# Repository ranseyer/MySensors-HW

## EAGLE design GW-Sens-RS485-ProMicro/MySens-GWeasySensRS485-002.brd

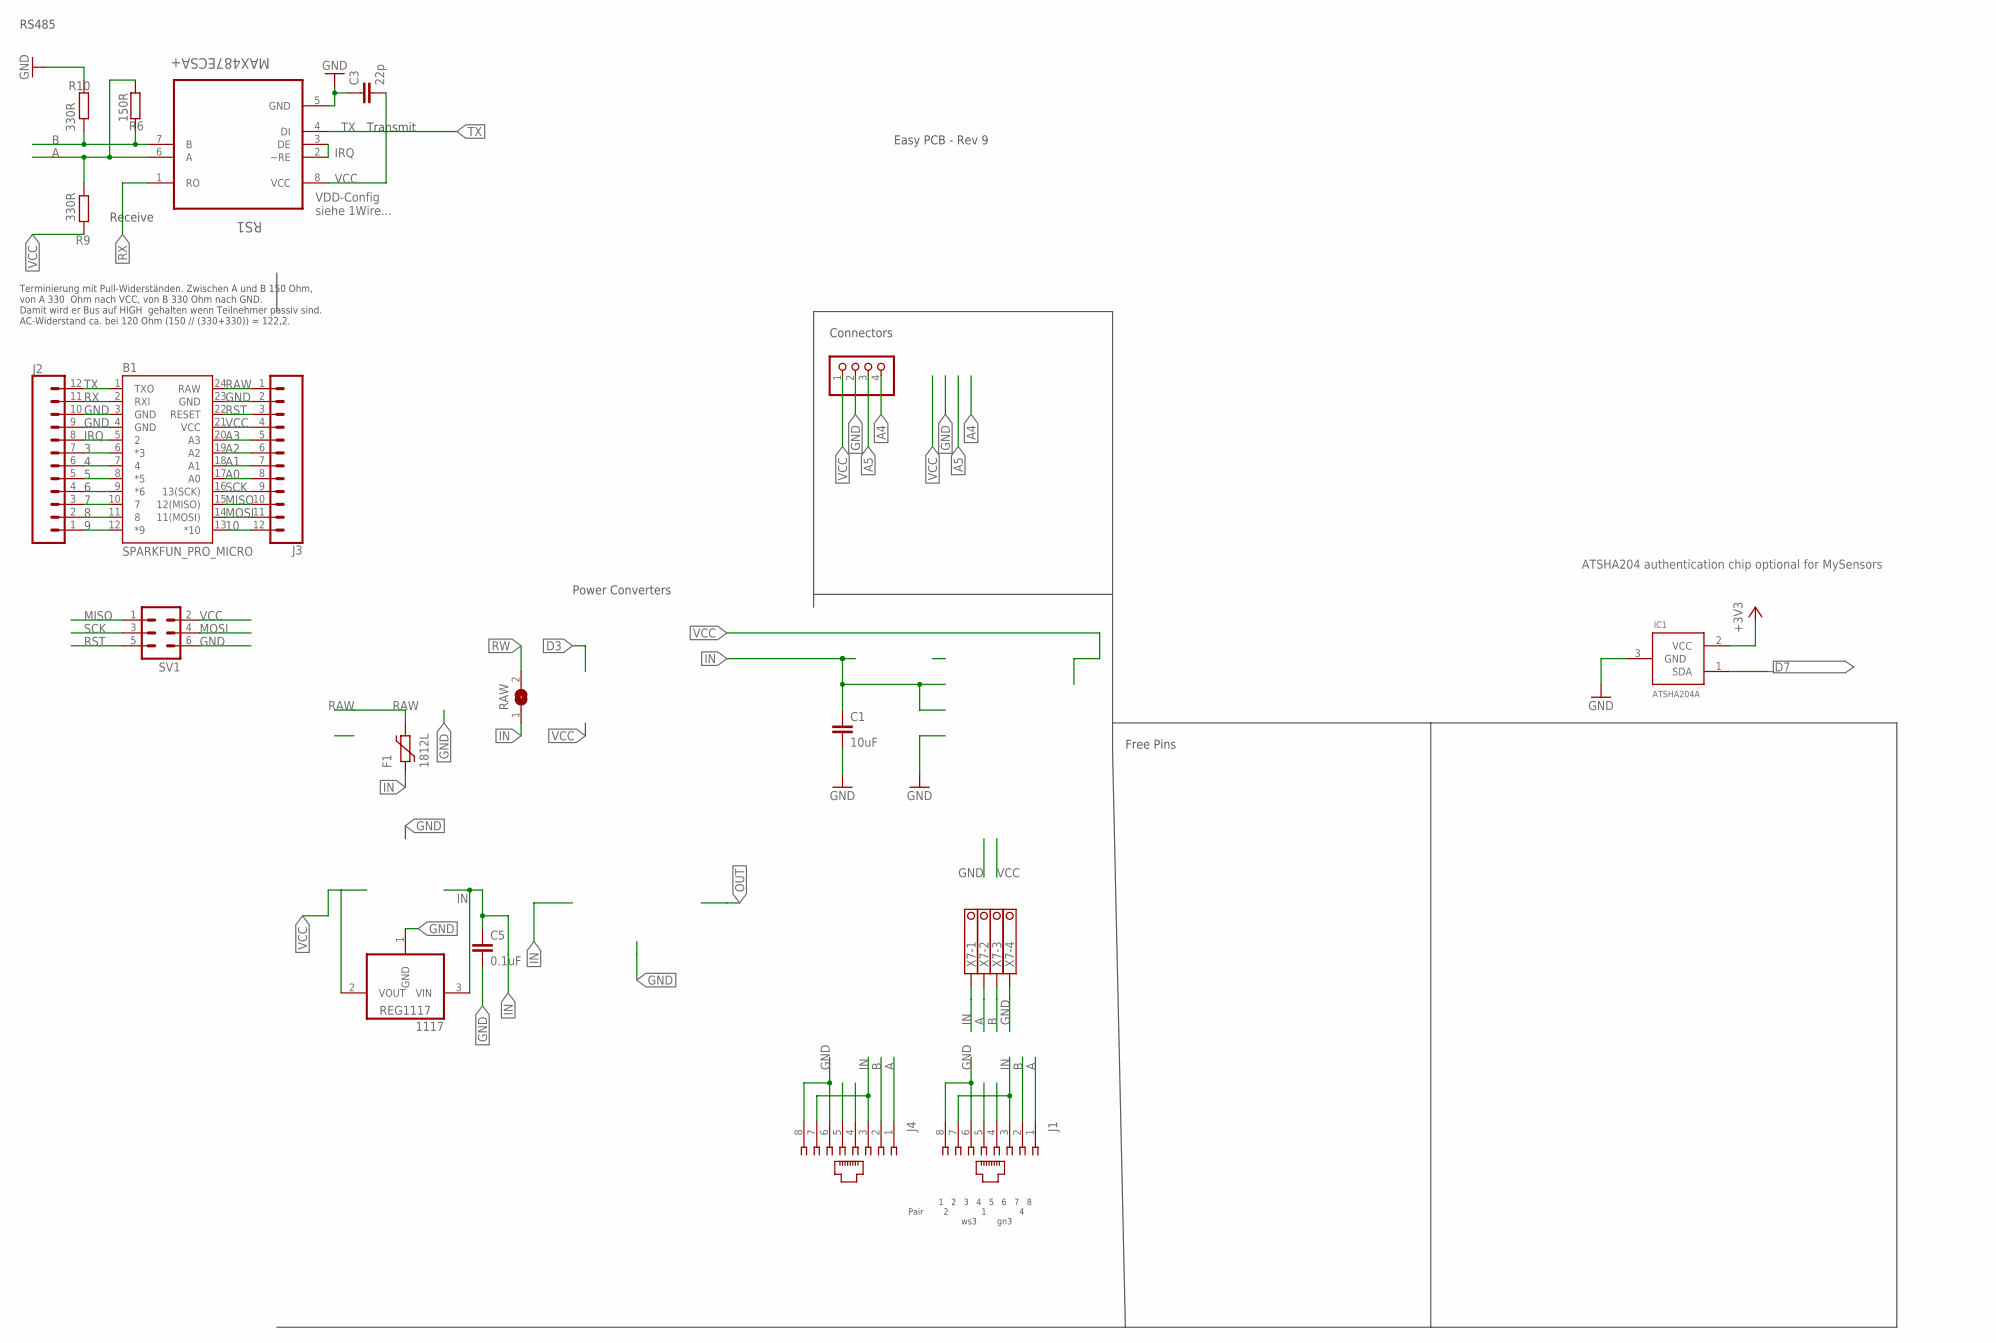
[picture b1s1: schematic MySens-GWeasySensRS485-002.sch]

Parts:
1117: REG1117; SOT223
B1: SPARKFUN_PRO_MICRO
C1: 10uF; 0805
C3: 22p; C0805
C5: 0.1uF; C1206
F1: 1812L
IC1: ATSHA204A; SOT23
J1, J4: 215878-2
J2, J3: CONN_12; 1X12
JP10: PINHD-1X04_2.54-S; 1X04-S
R6: 150R; R0805
R9, R10: 330R; R0805
RAW: SJ
RS1: MAX487ECSA+; SOIC127P600X175-8N
SV1: MA03-2
X7: 1751264

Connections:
3: B1.6 (*3), J2.7
3V3: IC1.2 (VCC)
4: B1.7 (4), J2.6
5: B1.8 (*5), J2.5
6: B1.9 (*6), J2.4
7: B1.10 (7), J2.3
8: B1.11 (8), J2.2
9: B1.12 (*9), J2.1
10: B1.13 (*10), J3.12
A: J1.1, J4.1, R6.1, R9.2, RS1.6 (A), X7.2
A0: B1.17 (A0), J3.8
A1: B1.18 (A1), J3.7
A2: B1.19 (A2), J3.6
A3: B1.20 (A3), J3.5
A4: JP10.4
A5: JP10.3
B: J1.2, J4.2, R6.2, R10.1, RS1.7 (B), X7.3
D7: IC1.1 (SDA)
GND: 1117.1 (GND), B1.3 (GND), B1.4 (GND), B1.23 (GND), C1.2, C3.1, C5.2, IC1.3 (GND), J1.6, J1.8, J2.9, J2.10, J3.2, J4.6, J4.8, JP10.2, R10.2, RS1.5 (GND), SV1.6, X7.4
IN: 1117.3 (VIN), C1.1, C5.1, F1.P$1 (1), J1.3, J1.7, J4.3, J4.7, RAW.1, X7.1
IRQ: B1.5 (2), J2.8, RS1.2 (~RE), RS1.3 (DE)
MISO: B1.15 (12(MISO)), J3.10, SV1.1
MOSI: B1.14 (11(MOSI)), J3.11, SV1.4
RAW: B1.24 (RAW), F1.P$2 (2), J3.1
RST: B1.22 (RESET), J3.3, SV1.5
RW: RAW.2
RX: B1.2 (RXI), J2.11, RS1.1 (RO)
SCK: B1.16 (13(SCK)), J3.9, SV1.3
TX: B1.1 (TXO), J2.12, RS1.4 (DI)
VCC: 1117.2 (VOUT), B1.21 (VCC), C3.2, J3.4, JP10.1, R9.1, RS1.8 (VCC), SV1.2

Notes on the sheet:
Easy PCB - Rev 9
Connectors
Power Converters
Free Pins
ATSHA204 authentication chip optional for MySensors
RS485
VDD-Config siehe 1Wire...
Terminierung mit Pull-Widerständen. Zwischen A und B 150 Ohm, von A 330 Ohm nach VCC, von B 330 Ohm nach GND. Damit wird er Bus auf HIGH gehalten wenn Teilnehmer passiv sind. AC-Widerstand ca. bei 120 Ohm (150 // (330+330)) = 122,2.
1 2 3 4 5 6 7 8 Pair 2 1 4 ws3 gn3
Transmit
Receive

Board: 2 copper layers, 19 parts (9 on the bottom side), 25 nets, no tracks yet.

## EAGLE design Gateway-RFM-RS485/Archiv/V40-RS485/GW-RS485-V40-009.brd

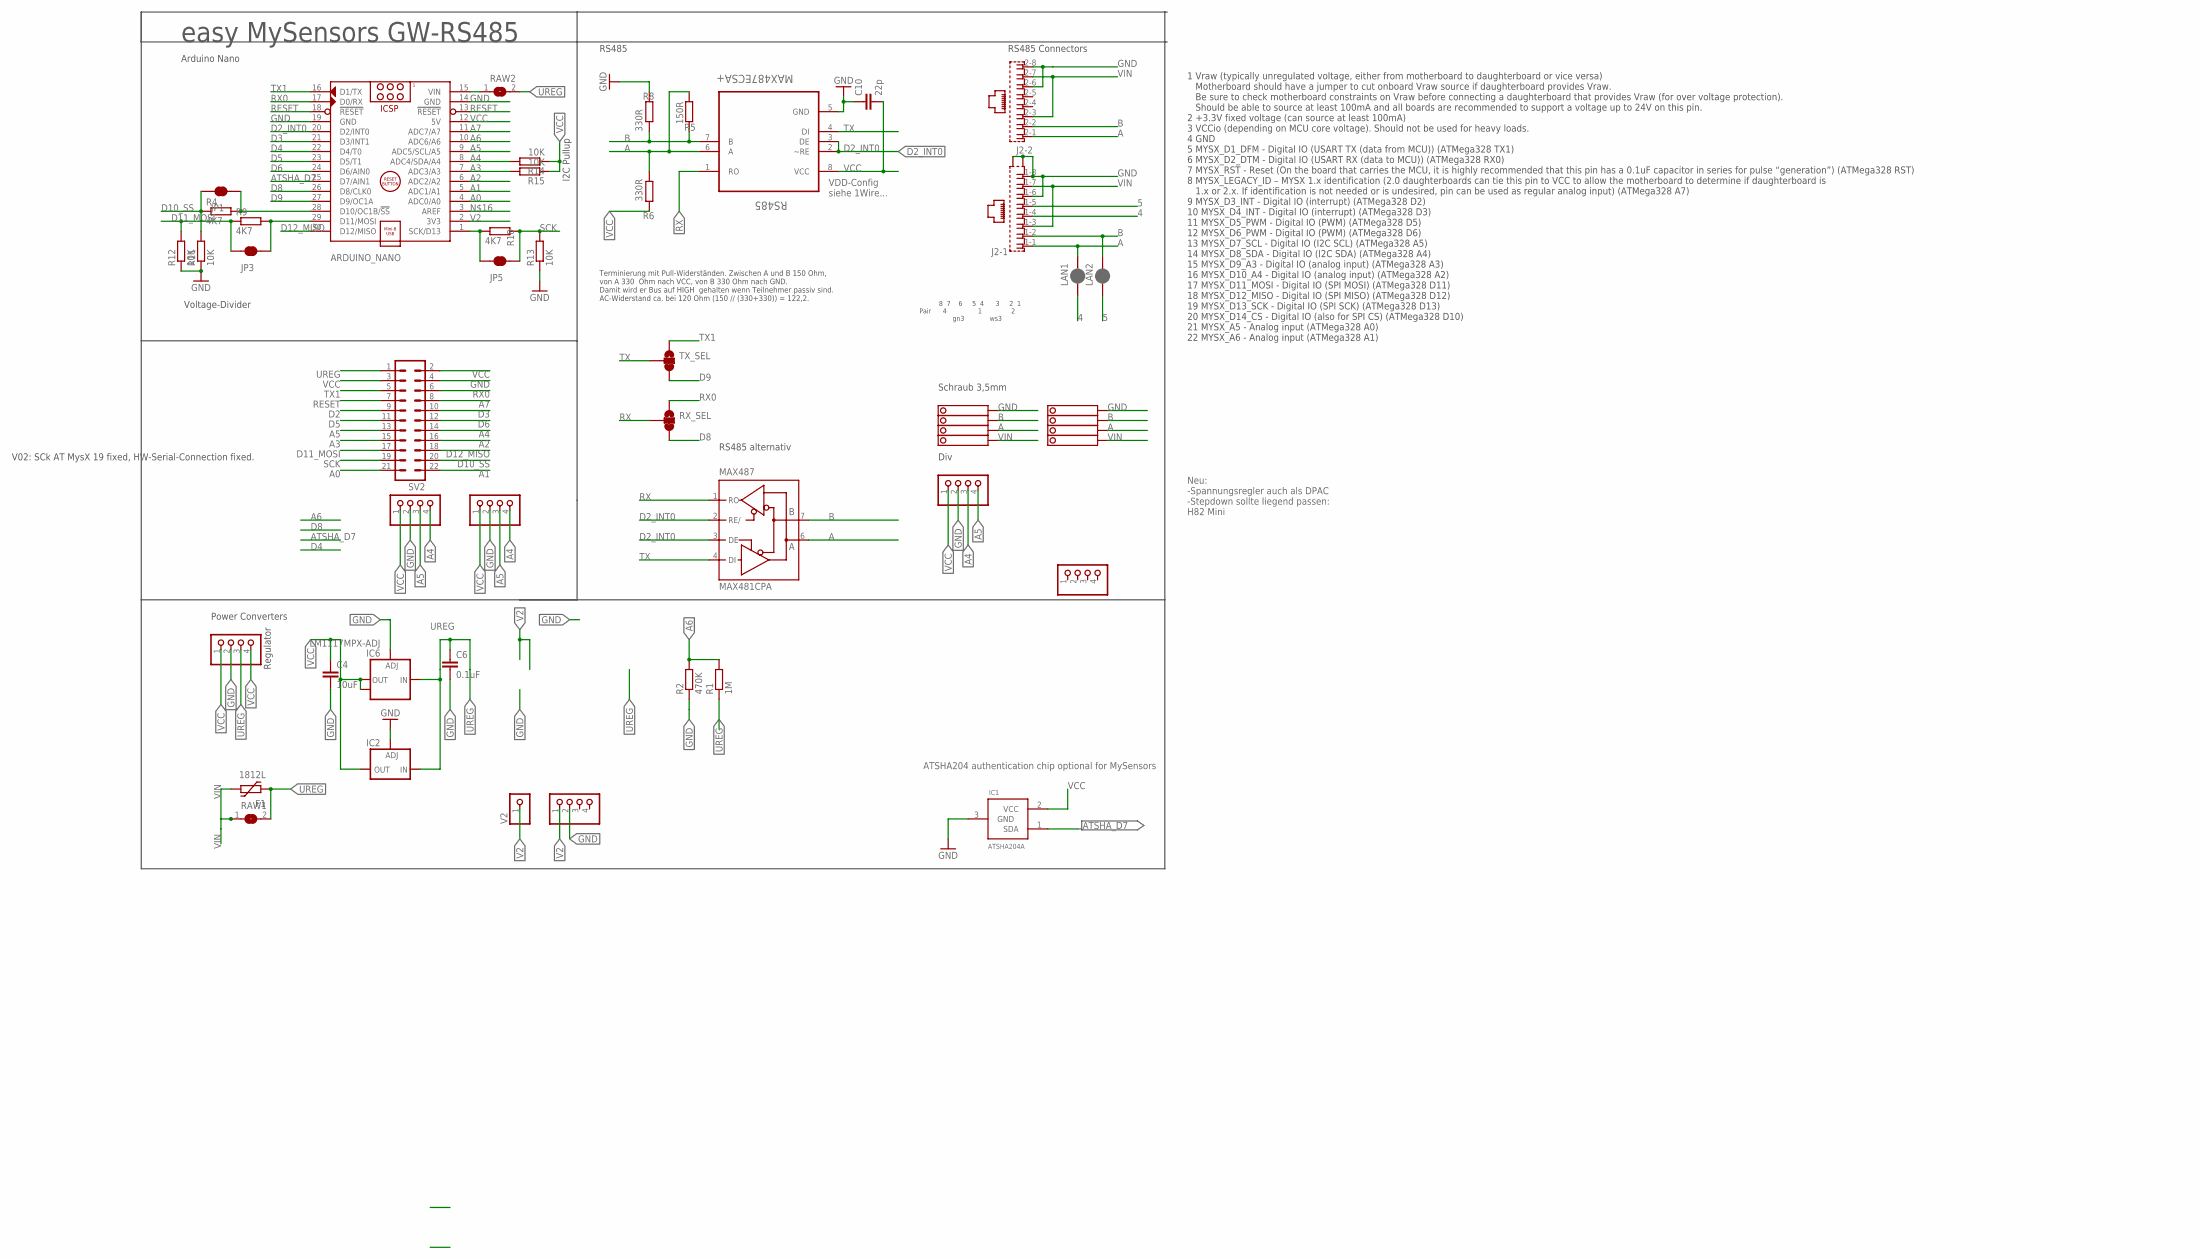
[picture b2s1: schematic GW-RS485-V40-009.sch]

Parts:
ARDUINO_NANO: ARDUINO_NANO_OHNE-BOHR; ARDUINO_NANO
BH1750: PINHD-1X04_2.54-S; 1X04-S
C4: 10uF; C1210
C6: 0.1uF; C1206
C10: 22p; C0805
F1: 1812L
I2C-1, I2C-2: PINHD-1X04_2.54-S; 1X04-S
IC1: ATSHA204A; SOT23
IC2: LD117ADT50TR; DPACK
IC6: LM1117MPX-ADJ; SOT223
J2: RJ45_2X_NARROW_SHILDPINS_NOCASE
JP1, JP3, JP5: JUMPER-SMT_2_NC_TRACE_SILK; SMT-JUMPER_2_NC_TRACE_SILK
JP2: PINHD-1X04_2.54-S; 1X04-S
LAN1, LAN2: JUMPER-SMT_2_NC_PASTE_SILK; SMT-JUMPER_2_NC_PASTE_SILK
MAX487: MAX481CPA; DIL08
R1: 1M; R0805
R2: 470K; R0805
R4, R9, R10: 4K7; M0805
R5: 150R; R0805
R6, R8: 330R; R0805
R11, R12, R13: 10K; M0805
R14, R15: 10K; R0805
RAW1, RAW2: SJ
RS485: MAX487ECSA+; SOIC127P600X175-8N
RX_SEL: JUMPER-SMT_3_1-NC_TRACE_SILK; SMT-JUMPER_3_1-NC_TRACE_SILK
STEPDWN: PINHD-1X04_2.54-S; 1X04-S
SV2: MA11-2
TX_SEL: JUMPER-SMT_3_1-NC_TRACE_SILK; SMT-JUMPER_3_1-NC_TRACE_SILK
V2: PINHD-1X1; 1X01
V2-: PINHD-1X04_2.54-S; 1X04-S
X1, X4: 1751264

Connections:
4: J2.1-4 (4), LAN1.1
5: J2.1-5 (5), LAN2.1
A: J2.1-1 (1), J2.2-1 (1), LAN1.2, MAX487.6 (A), R5.1, R6.2, RS485.6 (A), X1.2, X4.2
A0: ARDUINO_NANO.4 (ADC0/A0), SV2.21
A1: ARDUINO_NANO.5 (ADC1/A1), SV2.22
A2: ARDUINO_NANO.6 (ADC2/A2), SV2.16
A3: ARDUINO_NANO.7 (ADC3/A3), R15.2, SV2.15
A4: ARDUINO_NANO.8 (ADC4/SDA/A4), BH1750.4, I2C-1.4, I2C-2.3, R14.2, SV2.14
A5: ARDUINO_NANO.9 (ADC5/SCL/A5), BH1750.3, I2C-1.3, I2C-2.4, SV2.13
A6: ARDUINO_NANO.10 (ADC6/A6), R1.2, R2.2
A7: ARDUINO_NANO.11 (ADC7/A7), SV2.8
ATSHA_D7: ARDUINO_NANO.25 (D7/AIN1), IC1.1 (SDA)
B: J2.1-2 (2), J2.2-2 (2), LAN2.2, MAX487.7 (B), R5.2, R8.1, RS485.7 (B), X1.3, X4.3
D2: SV2.9
D2_INT0: ARDUINO_NANO.20 (D2/INT0), MAX487.2 (RE/), MAX487.3 (DE), RS485.2 (~RE), RS485.3 (DE)
D3: ARDUINO_NANO.21 (D3/INT1), SV2.10
D4: ARDUINO_NANO.22 (D4/T0)
D5: ARDUINO_NANO.23 (D5/T1), SV2.11
D6: ARDUINO_NANO.24 (D6/AIN0), SV2.12
D8: ARDUINO_NANO.26 (D8/CLK0), RX_SEL.3
D9: ARDUINO_NANO.27 (D9/OC1A), TX_SEL.3
D10_SS: JP1.1, R4.1, R11.2, SV2.20
D11_MOSI: JP3.1, R9.1, R12.2, SV2.17
D12_MISO: ARDUINO_NANO.30 (D12/MISO), SV2.18
GND: ARDUINO_NANO.14 (GND), ARDUINO_NANO.19 (GND), BH1750.2, C4.2, C6.2, C10.1, I2C-1.2, I2C-2.2, IC1.3 (GND), IC2.1 (ADJ), IC6.1 (ADJ), J2.1-6 (6), J2.1-8 (8), J2.2-6 (6), J2.2-8 (8), J2.G1 (S1), J2.G3 (S2), MAX487.5 (GND), R2.1, R8.2, R11.1, R12.1, R13.1, RS485.5 (GND), STEPDWN.2, SV2.4, V2-.2, X1.4, X4.4
unnamed: ARDUINO_NANO.1 (SCK/D13), JP5.1, R10.1
unnamed: ARDUINO_NANO.28 (D10/OC1B/!SS), JP1.2, R4.2
unnamed: ARDUINO_NANO.29 (D11/MOSI), JP3.2, R9.2
RAW1: ARDUINO_NANO.15 (VIN), RAW2.1
RESET: ARDUINO_NANO.13 (!RESET), ARDUINO_NANO.18 (!RESET), SV2.7
RX: MAX487.1 (RO), RS485.1 (RO), RX_SEL.2
RX0: ARDUINO_NANO.17 (D0/RX), RX_SEL.1, SV2.6
SCK: JP5.2, R10.2, R13.2, SV2.19
TX: MAX487.4 (DI), RS485.4 (DI), TX_SEL.2
TX1: ARDUINO_NANO.16 (D1/TX), SV2.5, TX_SEL.1
UREG: C6.1, F1.P$1 (1), IC2.3 (IN), IC6.3 (IN), R1.1, RAW1.2, RAW2.2, STEPDWN.3, SV2.1
V2: ARDUINO_NANO.2 (3V3), V2.1, V2-.1
VCC: ARDUINO_NANO.12 (5V), BH1750.1, C4.1, C10.2, I2C-1.1, I2C-2.1, IC1.2 (VCC), IC2.4 (OUT), IC6.2 (OUT), IC6.TAB (OUT1), MAX487.8 (VCC), R6.1, R14.1, R15.1, RS485.8 (VCC), STEPDWN.1, STEPDWN.4, SV2.2, SV2.3
VIN: F1.P$2 (2), J2.1-3 (3), J2.1-7 (7), J2.2-3 (3), J2.2-7 (7), RAW1.1, X1.1, X4.1

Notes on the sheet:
easy MySensors GW-RS485
Arduino Nano
ATSHA204 authentication chip optional for MySensors
Div
Neu: -Spannungsregler auch als DPAC -Stepdown sollte liegend passen: H82 Mini
Power Converters
RS485
VDD-Config siehe 1Wire...
Terminierung mit Pull-Widerständen. Zwischen A und B 150 Ohm, von A 330 Ohm nach VCC, von B 330 Ohm nach GND. Damit wird er Bus auf HIGH gehalten wenn Teilnehmer passiv sind. AC-Widerstand ca. bei 120 Ohm (150 // (330+330)) = 122,2.
Schraub 3,5mm
8 7 6 5 4 3 2 1 Pair 4 1 2 gn3 ws3
Regulator
RS485 Connectors
1 Vraw (typically unregulated voltage, either from motherboard to daughterboard or vice versa) Motherboard should have a jumper to cut onboard Vraw source if daughterboard provides Vraw. Be sure to check motherboard constraints on Vraw before connecting a daughterboard that provides Vraw (for over 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
Voltage-Divider
RS485 alternativ
I2C Pullup
V02: SCk AT MysX 19 fixed, HW-Serial-Connection fixed.

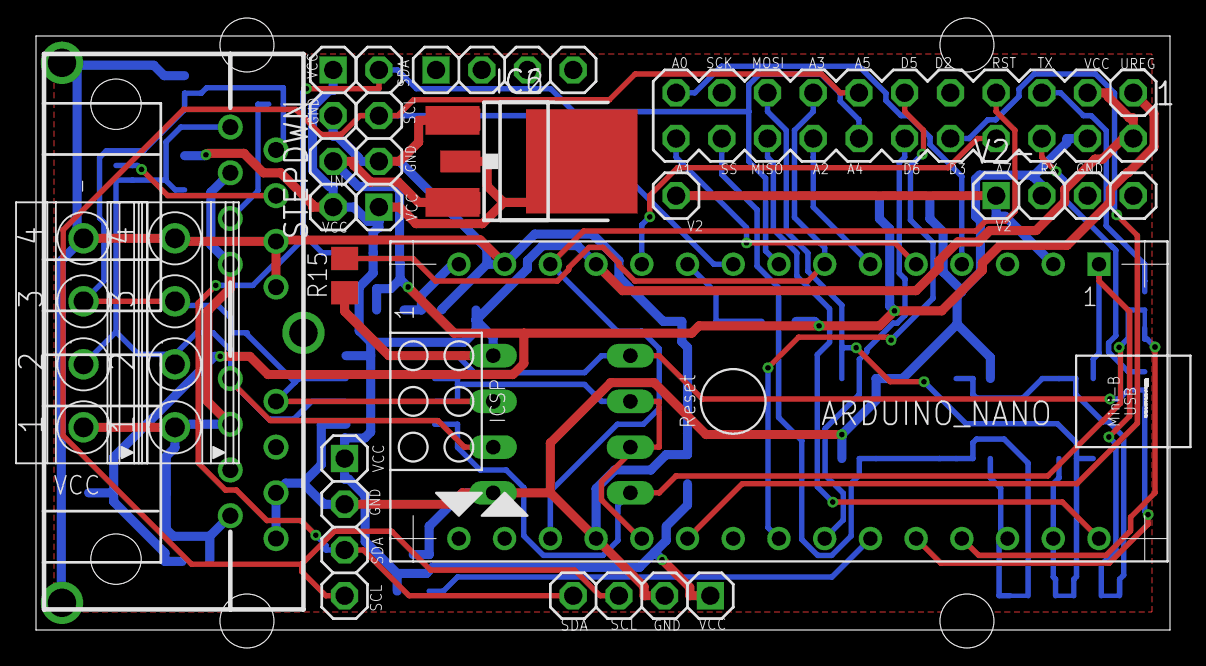
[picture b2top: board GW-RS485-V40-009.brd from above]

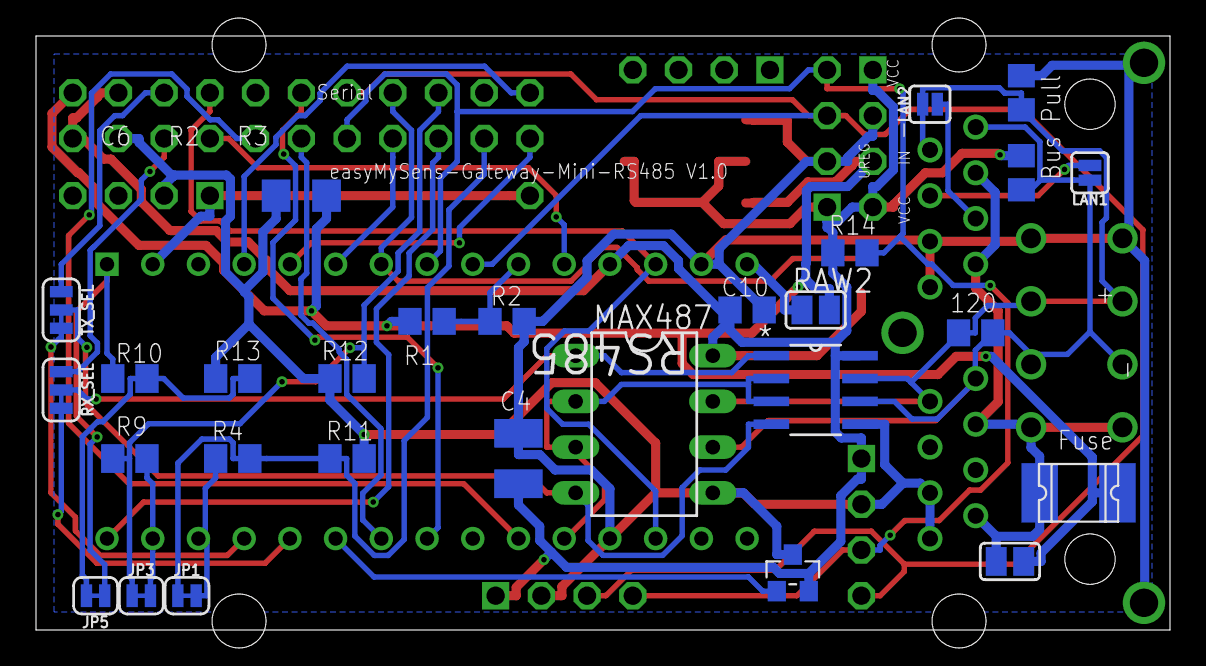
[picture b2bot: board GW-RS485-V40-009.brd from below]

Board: 2 copper layers, 63.0 x 33.0 mm, 43 parts (28 on the bottom side), 37 nets.

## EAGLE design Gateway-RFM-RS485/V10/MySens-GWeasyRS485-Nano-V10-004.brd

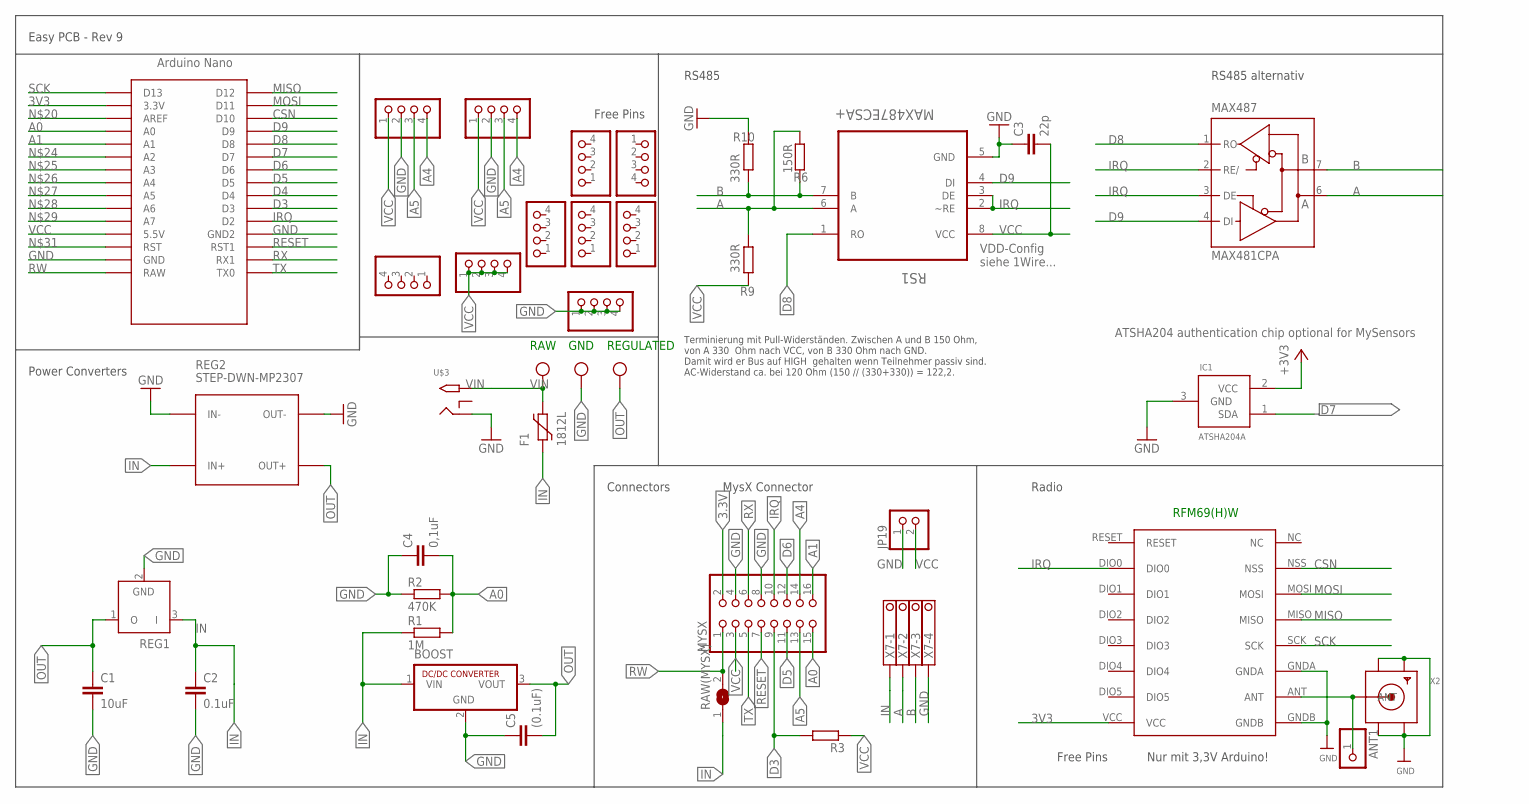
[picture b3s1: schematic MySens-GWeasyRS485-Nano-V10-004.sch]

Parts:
ANT1: PINHD-1X1; 1X01
BOOST: R-78C1.8-1.0; SIP3
C1: 10uF; C1210
C2: 0.1uF; C1206
C3: 22p; C0805
C4: 0,1uF; C1206
C5: (0.1uF); C1206
F1: 1812L
IC1: ATSHA204A; SOT23
JP1, JP3, JP6, JP10, JP11, JP12, JP13, JP14, JP15, JP16: PINHD-1X04_2.54-S; 1X04-S
JP19: PINHD-1X2; 1X02
MAX487: MAX481CPA; DIL08
MYSX: PINHD-2X08_2.54; 2X08
R1: 1M; R0805
R2: 470K; R0805
R3: R-EU_R0805; R0805
R6: 150R; R0805
R9, R10: 330R; R0805
RAW(MYSX): SJ
REG1: LP2950Z; TO92
REG2: STEP-DWN-MP2307; DC-DC-STEP-DOWN-MP2307
REGULATED: W237-103
RFM69W: RFM69HW; RFM
RS1: MAX487ECSA+; SOIC127P600X175-8N
U$2: NANO
U$3: 2.1MMJACKTHM; PJ-102A
X2: SMACONNECTOR_EDGE; SMA_EDGELAUNCH
X7: 1751264

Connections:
3.3V: MYSX.2
3V3: IC1.2 (VCC), RFM69W.VCC, U$2.3.3V
A: MAX487.6 (A), R6.1, R9.2, RS1.6 (A), X7.2
A0: C4.2, MYSX.15, R1.2, R2.2, U$2.A0
A1: MYSX.16, U$2.A1
A4: JP6.4, JP10.4, MYSX.14
A5: JP6.3, JP10.3, MYSX.13
B: MAX487.7 (B), R6.2, R10.1, RS1.7 (B), X7.3
CSN: RFM69W.NSS, U$2.D10
D3: MYSX.9, R3.2, U$2.D3
D4: U$2.D4
D5: MYSX.11, U$2.D5
D6: MYSX.12, U$2.D6
D7: IC1.1 (SDA), U$2.D7
D8: MAX487.1 (RO), RS1.1 (RO), U$2.D8
D9: MAX487.4 (DI), RS1.4 (DI), U$2.D9
GND: BOOST.2 (GND), C1.2, C2.2, C3.1, C4.1, C5.1, IC1.3 (GND), JP1.1, JP1.2, JP1.3, JP1.4, JP6.2, JP10.2, JP19.1, MAX487.5 (GND), MYSX.4, MYSX.8, R2.1, R10.2, REG1.2 (GND), REG2.IN-, REG2.OUT-, REGULATED.2, RFM69W.GNDA, RFM69W.GNDB, RS1.5 (GND), U$2.GND, U$2.GND1 (GND2), U$3.RING, X2.GND@1 (GND4), X2.GND@2 (GND3), X2.GND@3 (GND2), X2.GND@4 (GND1), X7.4
IN: BOOST.1 (VIN), C2.1, F1.P$1 (1), R1.1, RAW(MYSX).1, REG1.3 (I), REG2.IN+, X7.1
IRQ: MAX487.2 (RE/), MAX487.3 (DE), MYSX.10, RFM69W.DIO0, RS1.2 (~RE), RS1.3 (DE), U$2.D2
MISO: RFM69W.MISO, U$2.D12
MOSI: RFM69W.MOSI, U$2.D11
unnamed: ANT1.1, RFM69W.ANT, X2.P (ANT)
OUT: BOOST.3 (VOUT), C1.1, C5.2, REG1.1 (O), REG2.OUT+, REGULATED.1
RESET: MYSX.7, U$2.RST1
RW: MYSX.1, RAW(MYSX).2, U$2.RAW
RX: MYSX.6, U$2.RX1
SCK: RFM69W.SCK, U$2.D13
TX: MYSX.5, U$2.TX0
VCC: C3.2, JP3.1, JP3.2, JP3.3, JP3.4, JP6.1, JP10.1, JP19.2, MAX487.8 (VCC), MYSX.3, R3.1, R9.1, RS1.8 (VCC), U$2.5V (5.5V)
VIN: F1.P$2 (2), REGULATED.3, U$3.TIP

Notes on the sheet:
GND
RAW
REGULATED
Easy PCB - Rev 9
Connectors
Power Converters
Free Pins
ATSHA204 authentication chip optional for MySensors
RFM69(H)W
Nur mit 3,3V Arduino!
Radio
RS485
VDD-Config siehe 1Wire...
Terminierung mit Pull-Widerständen. Zwischen A und B 150 Ohm, von A 330 Ohm nach VCC, von B 330 Ohm nach GND. Damit wird er Bus auf HIGH gehalten wenn Teilnehmer passiv sind. AC-Widerstand ca. bei 120 Ohm (150 // (330+330)) = 122,2.
RS485 alternativ
MysX Connector

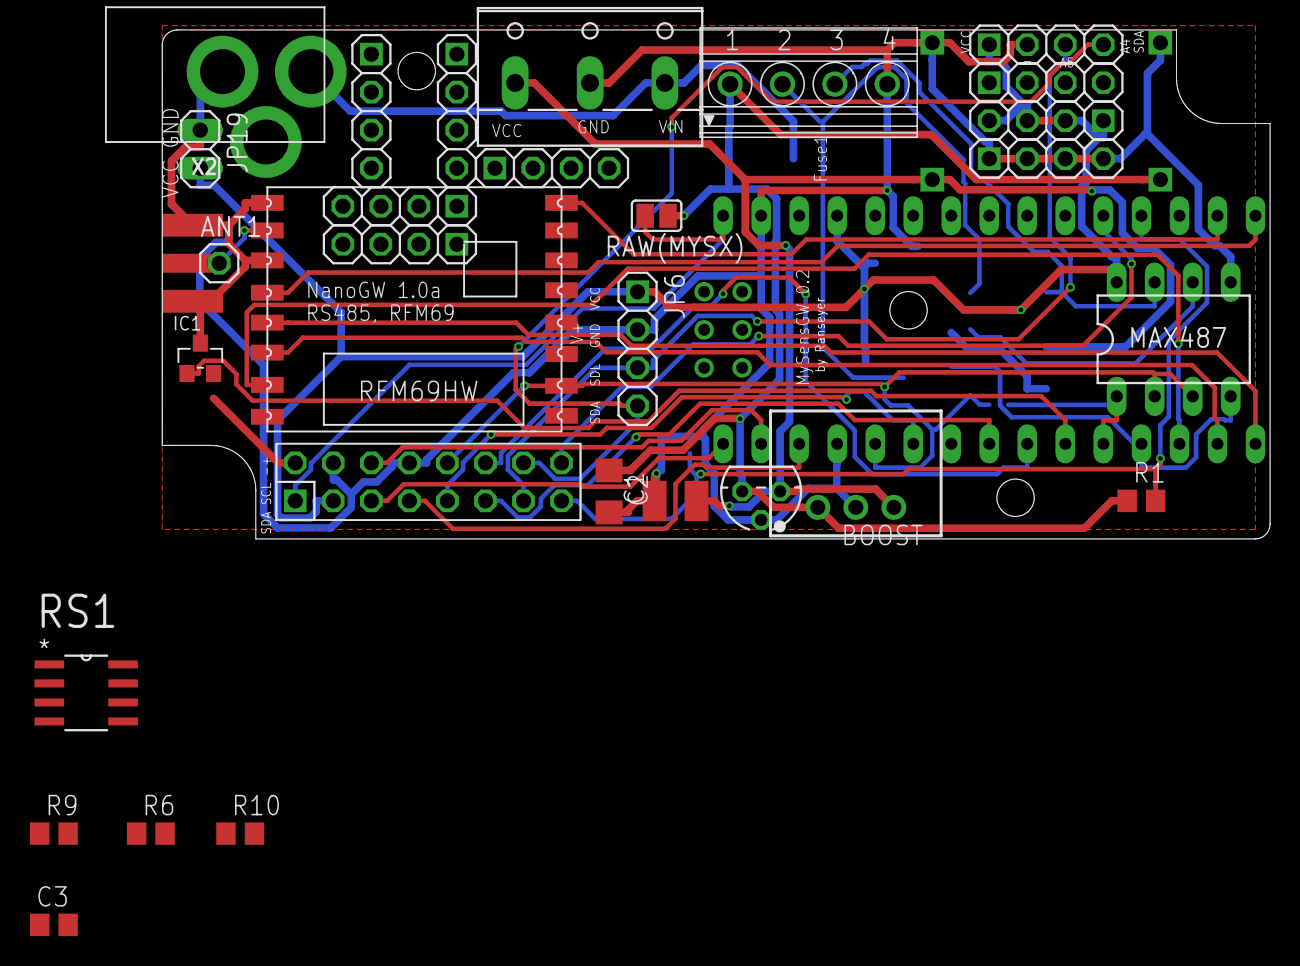
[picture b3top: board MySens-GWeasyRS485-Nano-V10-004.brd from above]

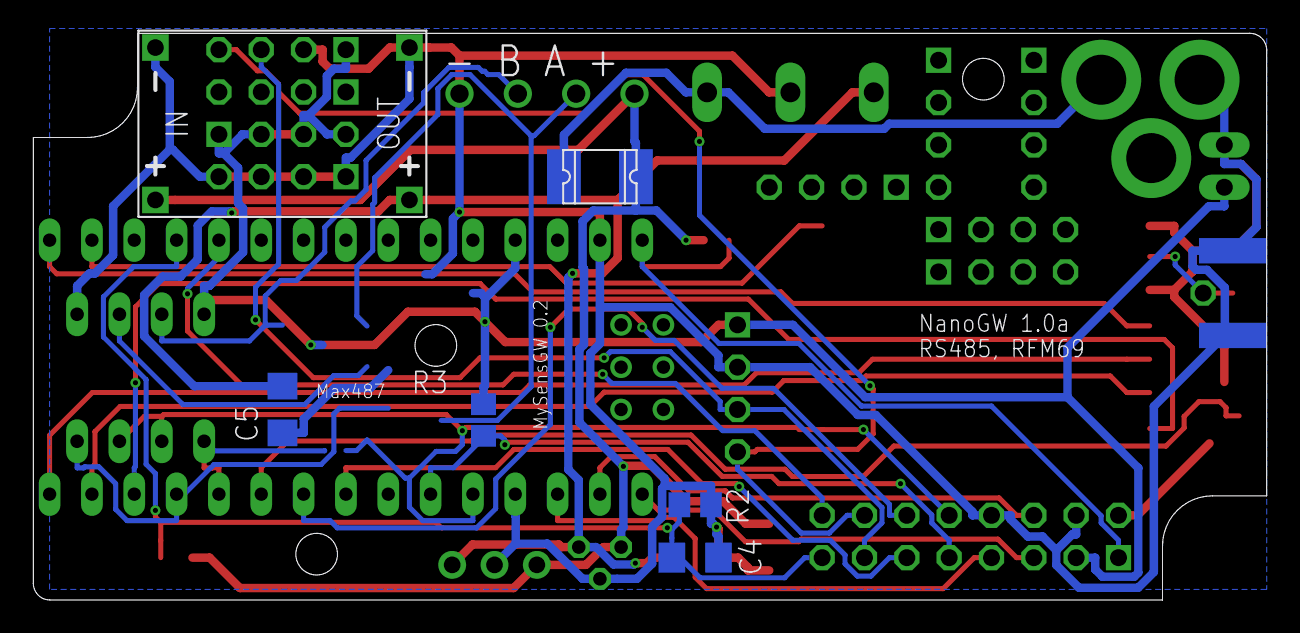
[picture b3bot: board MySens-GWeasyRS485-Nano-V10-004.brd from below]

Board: 2 copper layers, 74.0 x 34.0 mm, 38 parts (6 on the bottom side), 28 nets.

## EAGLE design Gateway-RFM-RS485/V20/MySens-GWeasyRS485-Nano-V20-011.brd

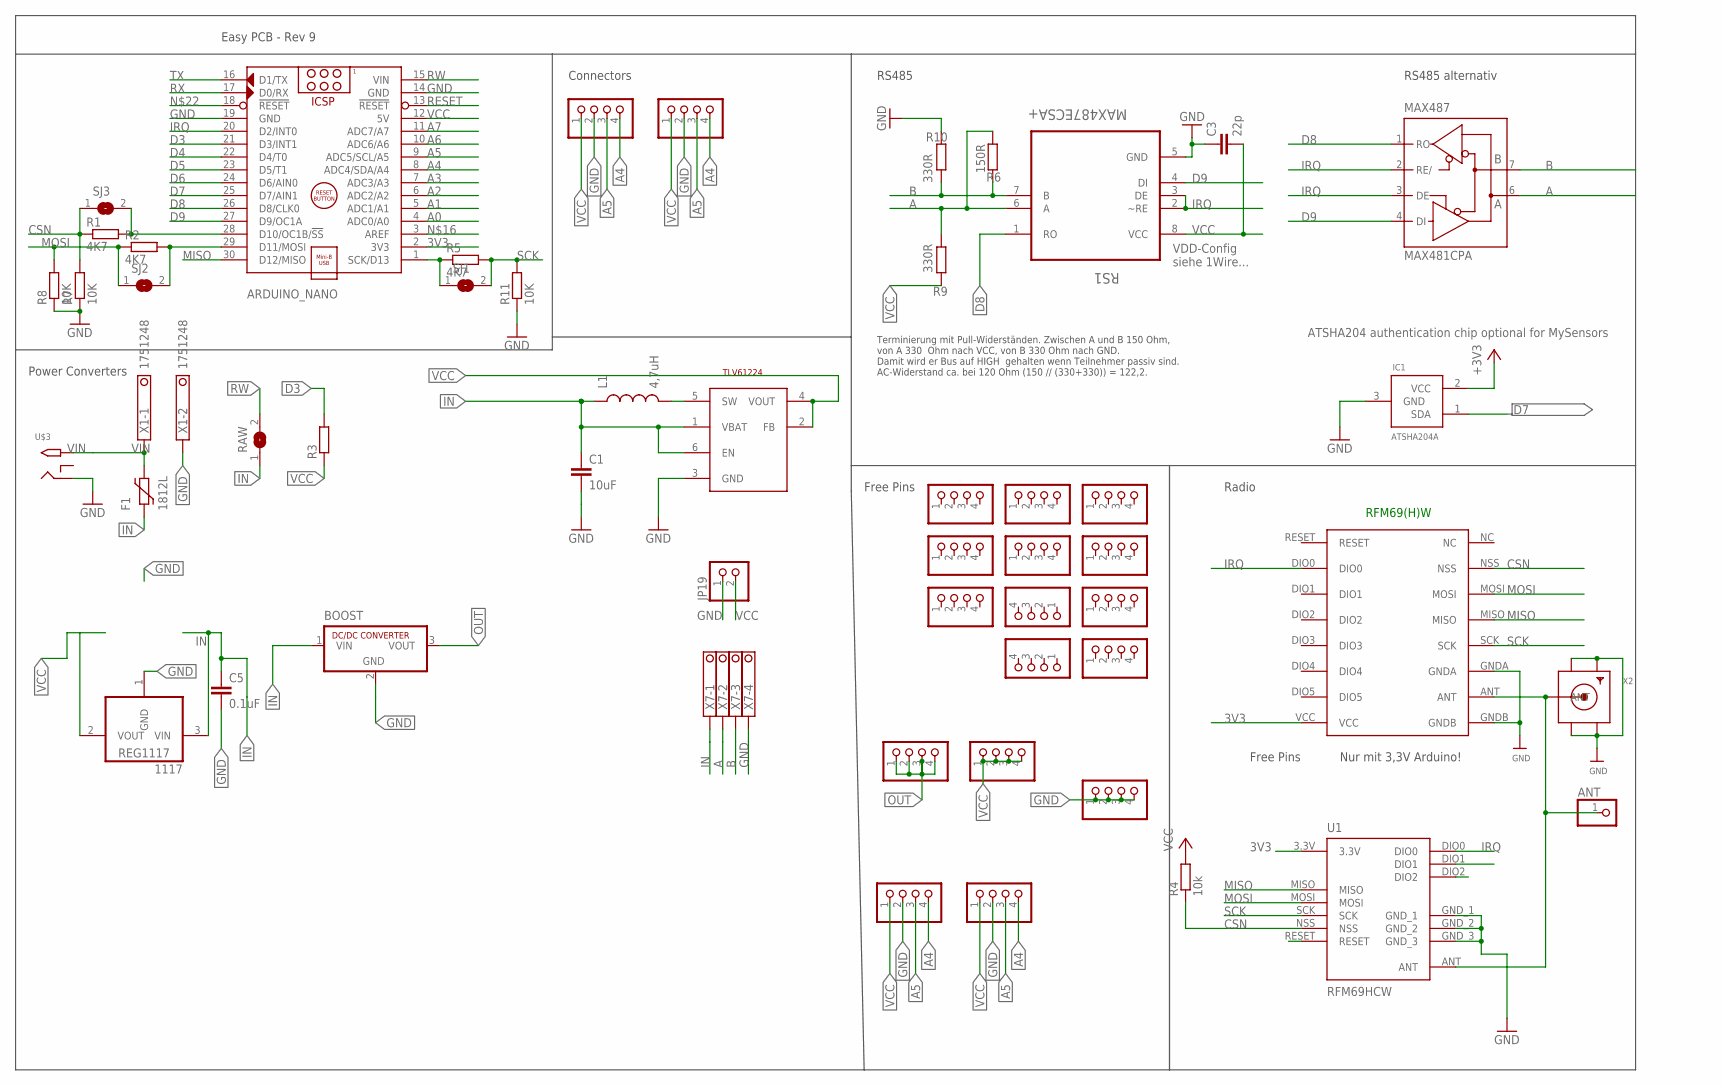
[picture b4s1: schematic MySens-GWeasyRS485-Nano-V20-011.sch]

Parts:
1117: REG1117; SOT223
ANT: PINHD-1X1; 1X01
ARDUINO_NANO: ARDUINO_NANO_OHNE-BOHR; ARDUINO_NANO
BOOST: R-78C1.8-1.0; SIP3
C1: 10uF; 0805
C3: 22p; C0805
C5: 0.1uF; C1206
F1: 1812L
IC1: ATSHA204A; SOT23
JP1, JP2, JP3, JP4, JP5, JP6, JP7, JP8, JP9, JP10, JP11, JP12, JP13, JP14, JP15, JP16, JP17, JP18: PINHD-1X04_2.54-S; 1X04-S
JP19: PINHD-1X2; 1X02
L1: 4,7uH; 0805
MAX487: MAX481CPA; DIL08
R1, R2, R5: 4K7; M0805
R3: R-EU_R0805; R0805
R4: 10k; M0805
R6: 150R; R0805
R7, R8, R11: 10K; M0805
R9, R10: 330R; R0805
RAW: SJ
RFM69W: RFM69HW; RFM
RS1: MAX487ECSA+; SOIC127P600X175-8N
SJ1, SJ2, SJ3: SJ
STEPUP: TLV61224; SOT23-6L
U1: RFM69HCW; RFM69HCW-XXXS2
U$3: 2.1MMJACKTHM; PJ-102A
X1: 1751248
X2: SMACONNECTOR_EDGE; SMA_EDGELAUNCH
X7: 1751264

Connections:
3V3: ARDUINO_NANO.2 (3V3), IC1.2 (VCC), RFM69W.VCC, U1.3.3V
A: MAX487.6 (A), R6.1, R9.2, RS1.6 (A), X7.2
A0: ARDUINO_NANO.4 (ADC0/A0)
A1: ARDUINO_NANO.5 (ADC1/A1)
A2: ARDUINO_NANO.6 (ADC2/A2)
A3: ARDUINO_NANO.7 (ADC3/A3)
A4: ARDUINO_NANO.8 (ADC4/SDA/A4), JP6.4, JP10.4, JP17.4, JP18.4
A5: ARDUINO_NANO.9 (ADC5/SCL/A5), JP6.3, JP10.3, JP17.3, JP18.3
A6: ARDUINO_NANO.10 (ADC6/A6)
A7: ARDUINO_NANO.11 (ADC7/A7)
ANT: ANT.1, RFM69W.ANT, U1.ANT, X2.P (ANT)
B: MAX487.7 (B), R6.2, R10.1, RS1.7 (B), X7.3
CSN: R1.1, R4.1, R7.2, RFM69W.NSS, SJ3.1, U1.NSS
D3: ARDUINO_NANO.21 (D3/INT1), R3.2
D4: ARDUINO_NANO.22 (D4/T0)
D5: ARDUINO_NANO.23 (D5/T1)
D6: ARDUINO_NANO.24 (D6/AIN0)
D7: ARDUINO_NANO.25 (D7/AIN1), IC1.1 (SDA)
D8: ARDUINO_NANO.26 (D8/CLK0), MAX487.1 (RO), RS1.1 (RO)
D9: ARDUINO_NANO.27 (D9/OC1A), MAX487.4 (DI), RS1.4 (DI)
GND: 1117.1 (GND), ARDUINO_NANO.14 (GND), ARDUINO_NANO.19 (GND), BOOST.2 (GND), C1.2, C3.1, C5.2, IC1.3 (GND), JP1.1, JP1.2, JP1.3, JP1.4, JP6.2, JP10.2, JP17.2, JP18.2, JP19.1, MAX487.5 (GND), R7.1, R8.1, R10.2, R11.1, RFM69W.GNDA, RFM69W.GNDB, RS1.5 (GND), STEPUP.3 (GND), U1.GND_1, U1.GND_2, U1.GND_3, U$3.RING, X1.2, X2.GND@1 (GND4), X2.GND@2 (GND3), X2.GND@3 (GND2), X2.GND@4 (GND1), X7.4
IN: 1117.3 (VIN), BOOST.1 (VIN), C1.1, C5.1, F1.P$1 (1), L1.1, RAW.1, STEPUP.1 (VBAT), STEPUP.6 (EN), X7.1
IRQ: ARDUINO_NANO.20 (D2/INT0), MAX487.2 (RE/), MAX487.3 (DE), RFM69W.DIO0, RS1.2 (~RE), RS1.3 (DE), U1.DIO0
MISO: ARDUINO_NANO.30 (D12/MISO), RFM69W.MISO, U1.MISO
MOSI: R2.1, R8.2, RFM69W.MOSI, SJ2.1, U1.MOSI
unnamed: ARDUINO_NANO.1 (SCK/D13), R5.1, SJ1.1
unnamed: ARDUINO_NANO.28 (D10/OC1B/!SS), R1.2, SJ3.2
unnamed: ARDUINO_NANO.29 (D11/MOSI), R2.2, SJ2.2
unnamed: L1.2, STEPUP.5 (SW)
OUT: BOOST.3 (VOUT), JP13.1, JP13.2, JP13.3, JP13.4
RESET: ARDUINO_NANO.13 (!RESET)
RW: ARDUINO_NANO.15 (VIN), RAW.2
RX: ARDUINO_NANO.17 (D0/RX)
SCK: R5.2, R11.2, RFM69W.SCK, SJ1.2, U1.SCK
TX: ARDUINO_NANO.16 (D1/TX)
VCC: 1117.2 (VOUT), ARDUINO_NANO.12 (5V), C3.2, JP3.1, JP3.2, JP3.3, JP3.4, JP6.1, JP10.1, JP17.1, JP18.1, JP19.2, MAX487.8 (VCC), R3.1, R4.2, R9.1, RS1.8 (VCC), STEPUP.2 (FB), STEPUP.4 (VOUT)
VIN: F1.P$2 (2), U$3.TIP, X1.1

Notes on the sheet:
Easy PCB - Rev 9
Connectors
Power Converters
Free Pins
ATSHA204 authentication chip optional for MySensors
RFM69(H)W
Nur mit 3,3V Arduino!
Radio
RS485
VDD-Config siehe 1Wire...
Terminierung mit Pull-Widerständen. Zwischen A und B 150 Ohm, von A 330 Ohm nach VCC, von B 330 Ohm nach GND. Damit wird er Bus auf HIGH gehalten wenn Teilnehmer passiv sind. AC-Widerstand ca. bei 120 Ohm (150 // (330+330)) = 122,2.
RS485 alternativ

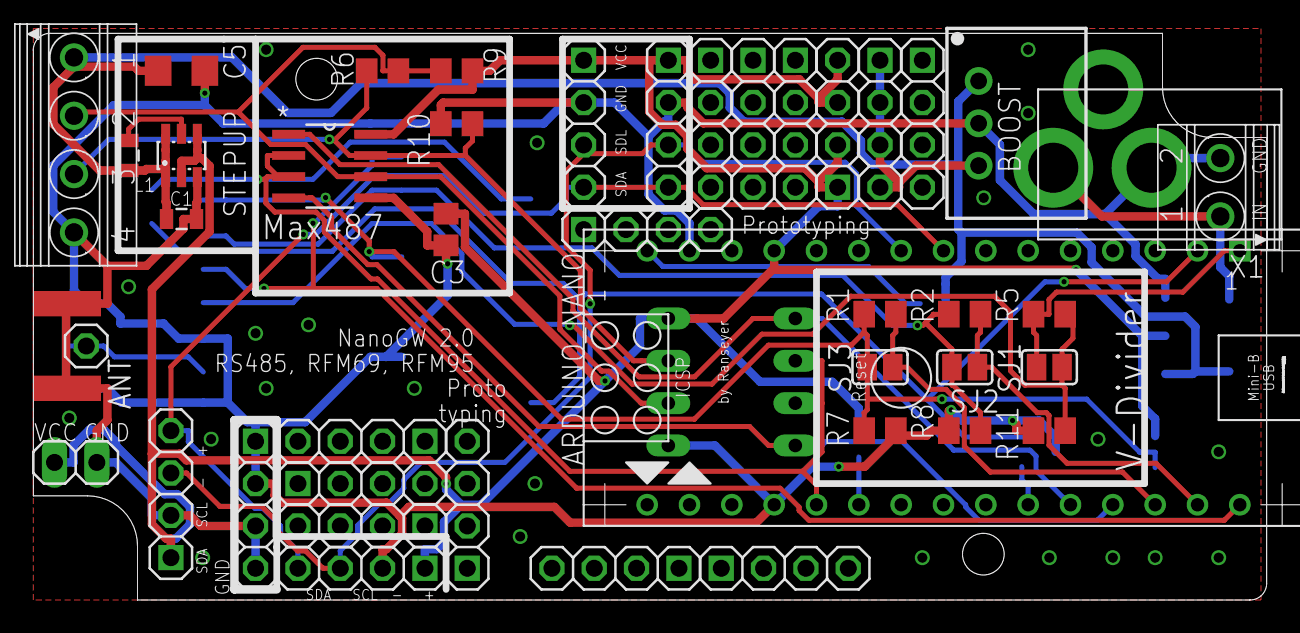
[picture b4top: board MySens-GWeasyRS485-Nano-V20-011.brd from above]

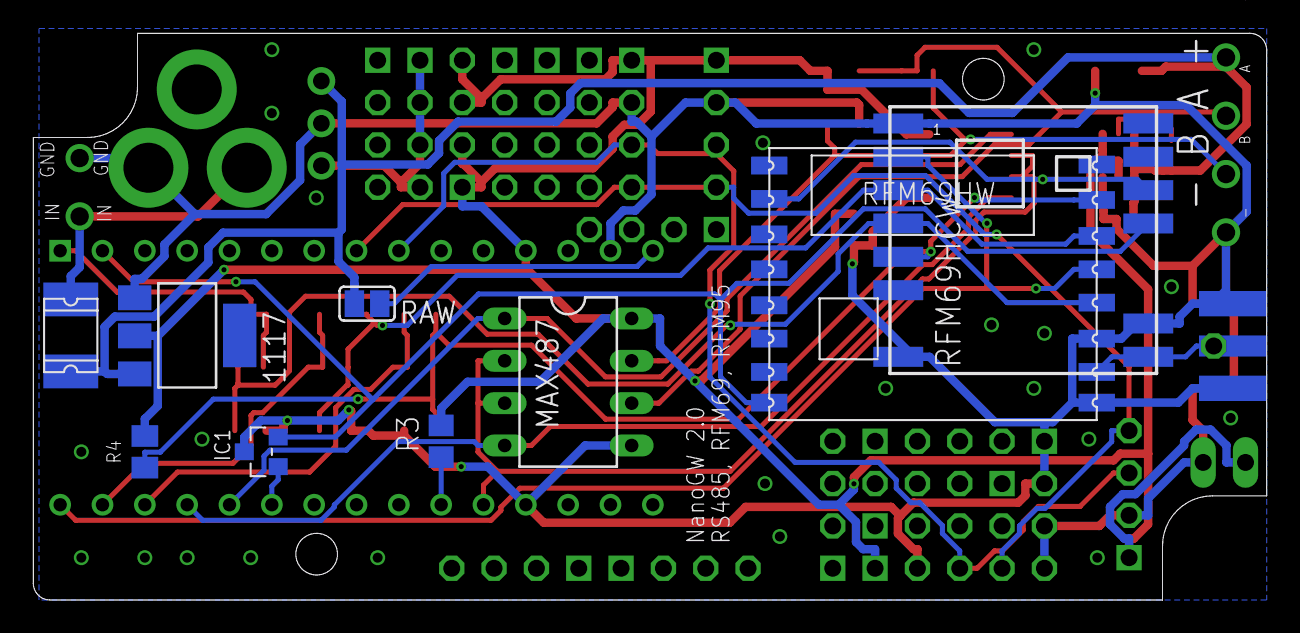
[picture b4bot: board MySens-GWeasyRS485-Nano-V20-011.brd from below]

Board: 2 copper layers, 74.0 x 34.0 mm, 53 parts (10 on the bottom side), 25 nets.

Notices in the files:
parts and their libraries:
SparkFun-Passives: Licensing: CC v3.0 Share-Alike You are welcome to use this library for commercial purposes.
SparkFun-Boards: Licensing: Creative Commons ShareAlike 4.0 International - https://creativecommons.org/licenses/by-sa/4.0
